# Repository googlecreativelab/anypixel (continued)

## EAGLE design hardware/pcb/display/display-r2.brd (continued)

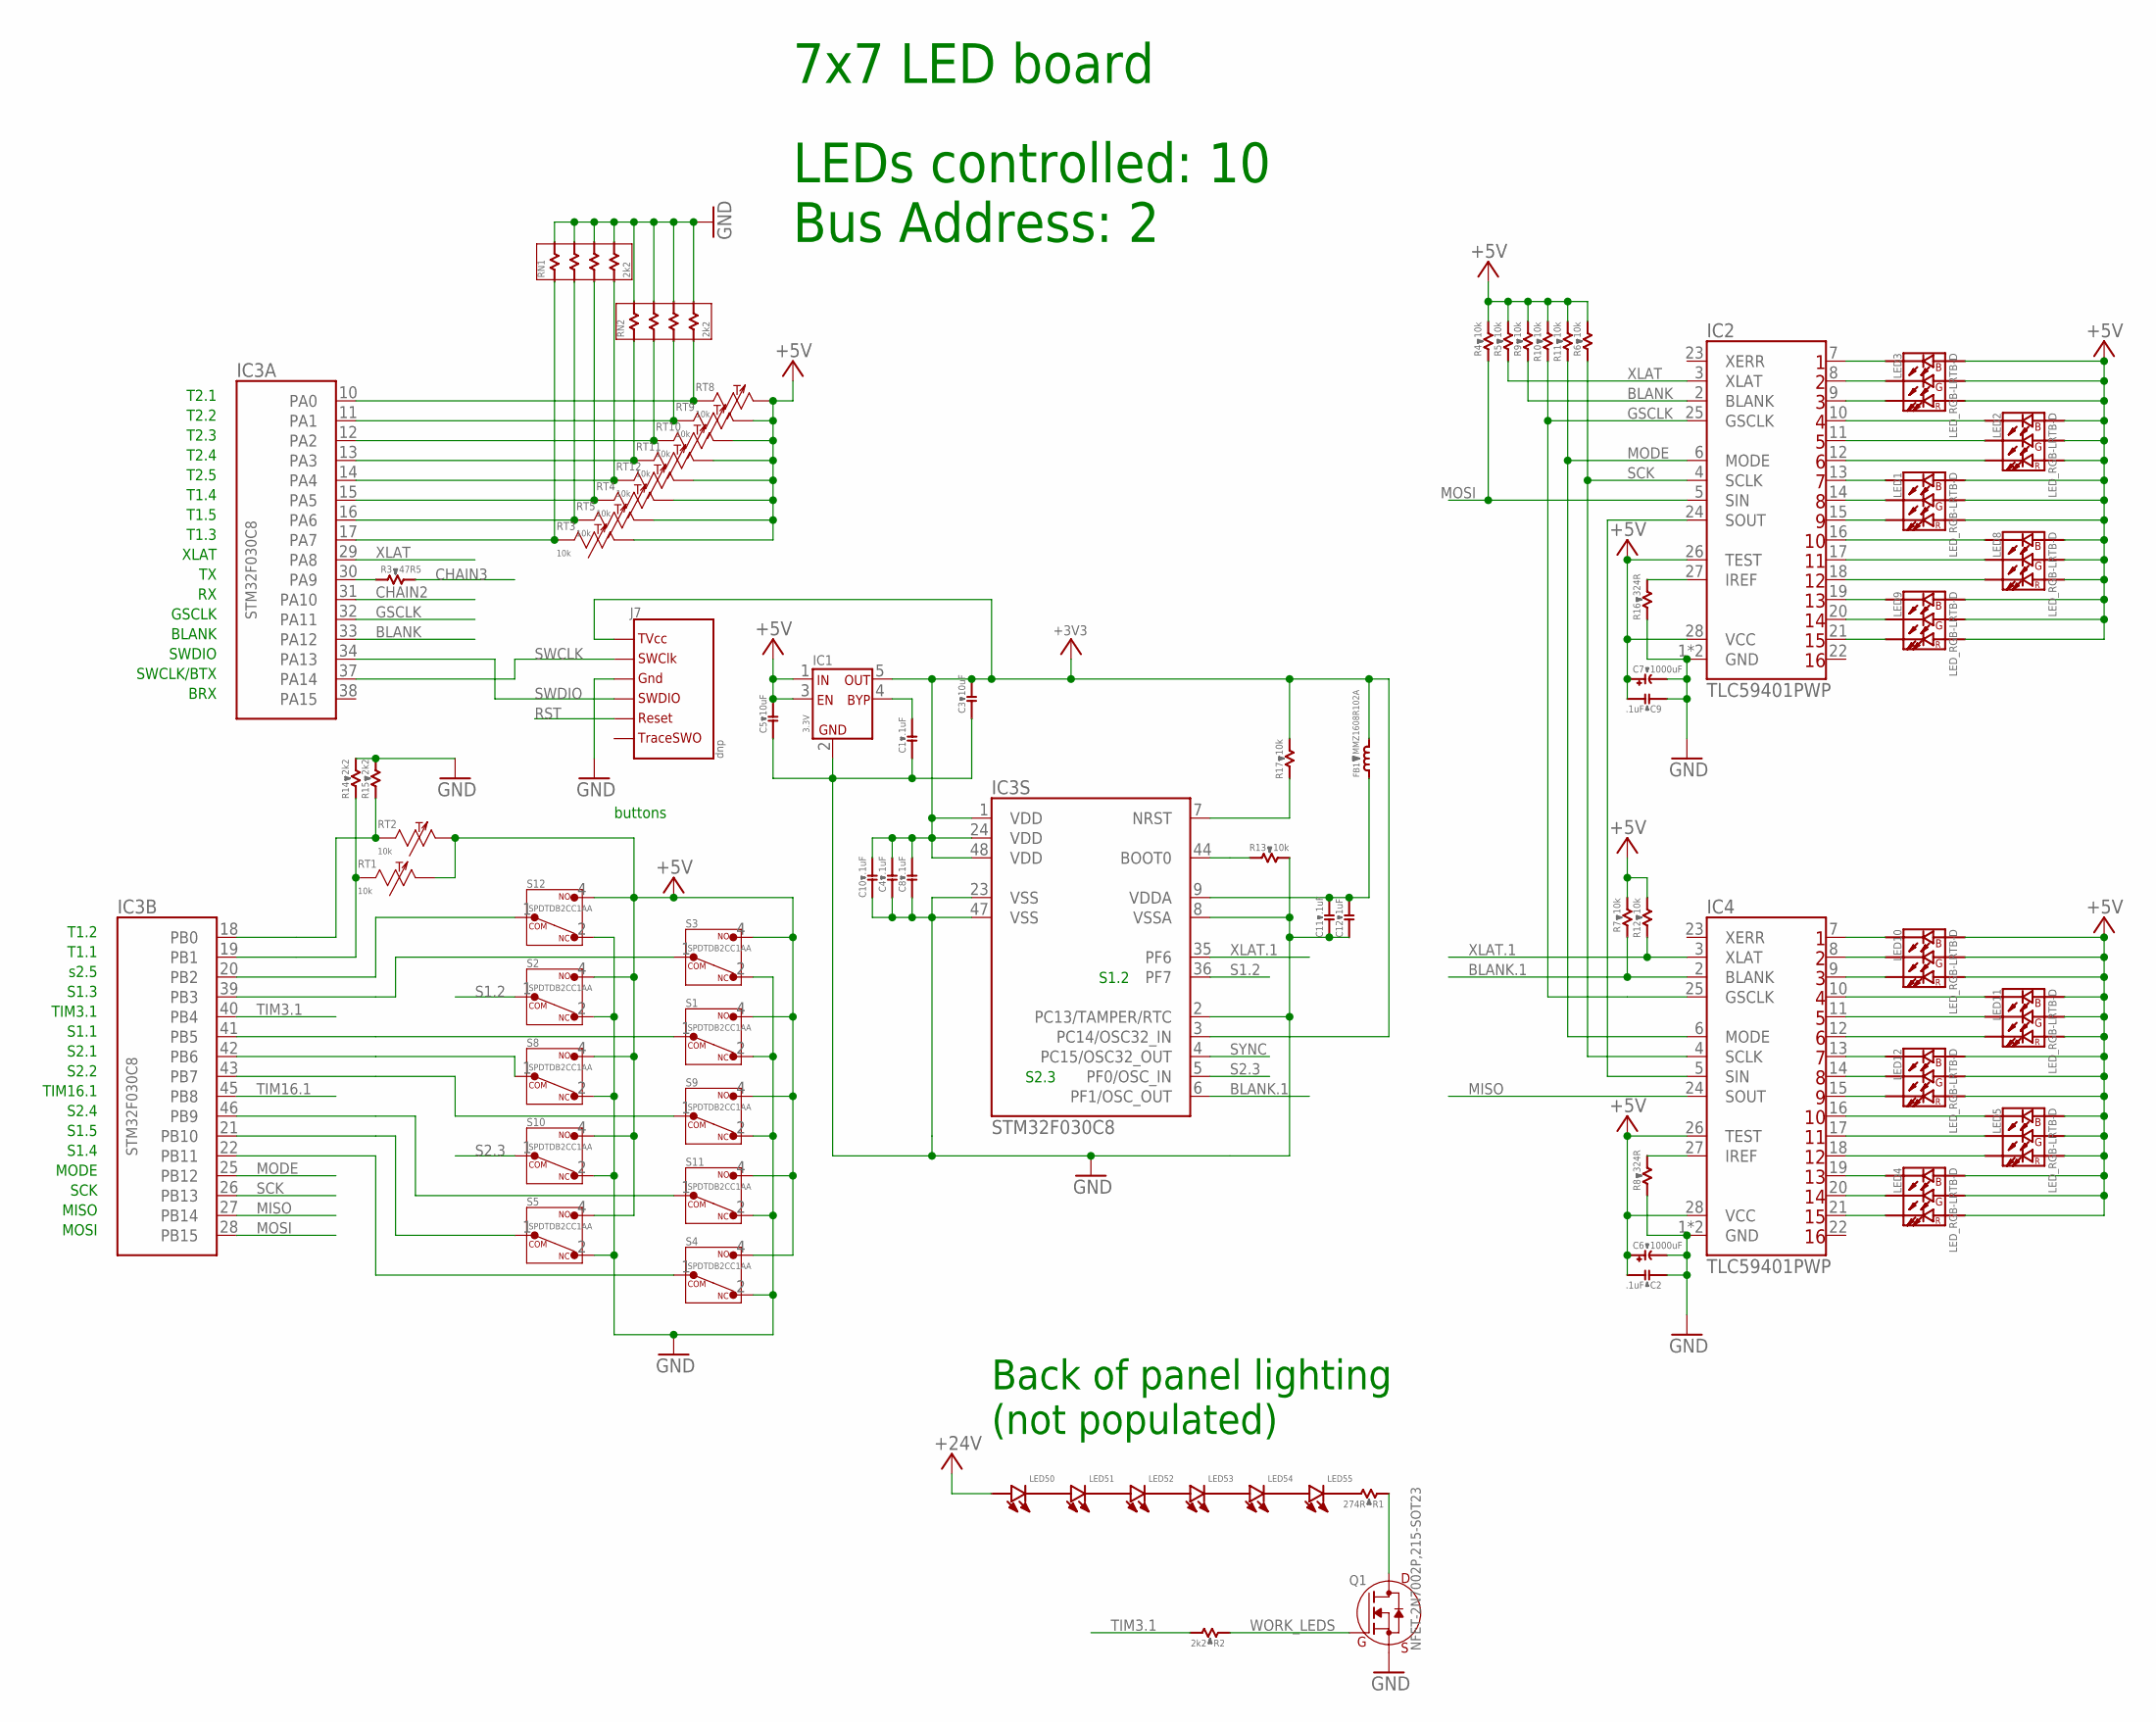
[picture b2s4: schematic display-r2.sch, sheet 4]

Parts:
C1, C2, C4, C8, C9, C10, C11: .1uF; C0603B; PARTNO CGA3E2X7R1H104K080AA
C3, C5: 10uF; C0603B; PARTNO C1608X6S1A106M080AC
C6, C7: 1000uF; E5-10,5; PARTNO EKZN160ELL102MJ16S
C12: 1uF; C0603B; PARTNO CGA3E3X5R1H105K080AB
FB1: MMZ1608R102A; R0603B; PARTNO MMZ1608R102A
IC1: 3.3V; SOT-23-5; PARTNO TC2185-3.3VCTTR
IC2, IC4: TLC59401PWP; TSSOP28_PAD; PARTNO TLC59401PWPR
IC3: STM32F030C8; LQFP-48; PARTNO STM32F030C8T6
J7: dnp; TC2030-IDC-NL
LED1, LED2, LED3, LED4, LED5, LED8, LED9, LED10, LED11, LED12: LED_RGB-LRTB-D; LRTB_C9TP-D; PARTNO LRTBC9TP-CWD5-1+D5E7-25+A
LED50, LED51, LED52, LED53, LED54, LED55: LED-LTW-006DCG; LTW-006DCG; PARTNO LTW-006DCG-E2
Q1: NFET-2N7002P,215-SOT23; SOT-23; PARTNO 2N7002P,215
R1: 274R; R0805B; PARTNO CRCW0805274RFKEA
R2, R14, R15: 2k2; R0603B; PARTNO CRCW06032K20FKEA
R3: 47R5; R0603B; PARTNO CRCW060347R5FKEA
R4, R5, R6, R7, R9, R10, R11, R12, R13, R17: 10k; R0603B; PARTNO CRCW060310K0FKEA
R8, R16: 324R; R0603B; PARTNO CRCW0603324RFKEA
RN1, RN2: 2k2; CAY16; PARTNO CAY16-2201F4LF
RT1, RT2, RT3, RT4, RT5, RT8, RT9, RT10, RT11, RT12: 10k; R0603Y; PARTNO NCP18XH103F03RB
S1, S2, S3, S4, S5, S8, S9, S10, S11, S12: SPDTDB2CC1AA; DB2CC1AA; PARTNO DB2CC1AA

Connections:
+3V3: C3.2, C4.2, C8.2, C10.2, FB1.2, IC1.5 (OUT), IC3.1 (VDD), IC3.3 (PC14/OSC32_IN), IC3.24 (VDD), IC3.48 (VDD), J7.1 (TVCC), R17.2
+5V: C2.2, C5.2, C6.+, C7.+, C9.2, IC1.1 (IN), IC1.3 (EN), IC2.26 (TEST), IC2.28 (VCC), IC4.26 (TEST), IC4.28 (VCC), LED1.A1 (ANODE_R), LED1.A2 (ANODE_G), LED1.A3 (ANODE_B), LED2.A1 (ANODE_R), LED2.A2 (ANODE_G), LED2.A3 (ANODE_B), LED3.A1 (ANODE_R), LED3.A2 (ANODE_G), LED3.A3 (ANODE_B), LED4.A1 (ANODE_R), LED4.A2 (ANODE_G), LED4.A3 (ANODE_B), LED5.A1 (ANODE_R), LED5.A2 (ANODE_G), LED5.A3 (ANODE_B), LED8.A1 (ANODE_R), LED8.A2 (ANODE_G), LED8.A3 (ANODE_B), LED9.A1 (ANODE_R), LED9.A2 (ANODE_G), LED9.A3 (ANODE_B), LED10.A1 (ANODE_R), LED10.A2 (ANODE_G), LED10.A3 (ANODE_B), LED11.A1 (ANODE_R), LED11.A2 (ANODE_G), LED11.A3 (ANODE_B), LED12.A1 (ANODE_R), LED12.A2 (ANODE_G), LED12.A3 (ANODE_B), R4.2, R5.2, R6.2, R7.2, R9.2, R10.2, R11.2, R12.2, RT1.2, RT2.2, RT3.2, RT4.2, RT5.2, RT8.2, RT9.2, RT10.2, RT11.2, RT12.2, S1.4 (NO), S2.4 (NO), S3.4 (NO), S4.4 (NO), S5.4 (NO), S8.4 (NO), S9.4 (NO), S10.4 (NO), S11.4 (NO), S12.4 (NO); also elsewhere on the board
+24V: LED50.A (ANODE); also elsewhere on the board
BLANK: IC2.2 (BLANK), IC3.33 (PA12), R9.1
BLANK.1: IC3.6 (PF1/OSC_OUT), IC4.2 (BLANK), R7.1
CHAIN2: IC3.31 (PA10); also elsewhere on the board
CHAIN3: R3.2; also elsewhere on the board
GND: C1.1, C2.1, C3.1, C4.1, C5.1, C6.-, C7.-, C8.1, C9.1, C10.1, C11.1, C12.1, IC1.2 (GND), IC2.1 (GND), IC2.PAD (GND), IC3.2 (PC13/TAMPER/RTC), IC3.8 (VSSA), IC3.23 (VSS), IC3.47 (VSS), IC4.1 (GND), IC4.PAD (GND), J7.5 (GND), Q1.2 (S), R8.1, R13.2, R14.2, R15.2, R16.1, RN1.A2, RN1.B2, RN1.C2, RN1.D2, RN2.A2, RN2.B2, RN2.C2, RN2.D2, S1.2 (NC), S2.2 (NC), S3.2 (NC), S4.2 (NC), S5.2 (NC), S8.2 (NC), S9.2 (NC), S10.2 (NC), S11.2 (NC), S12.2 (NC); also elsewhere on the board
GSCLK: IC2.25 (GSCLK), IC3.32 (PA11), IC4.25 (GSCLK), R10.1
MISO: IC3.27 (PB14), IC4.24 (SOUT)
MODE: IC2.6 (MODE), IC3.25 (PB12), IC4.6 (MODE), R11.1
MOSI: IC2.5 (SIN), IC3.28 (PB15), R4.1
unnamed: IC3.44 (BOOT0), R13.1
unnamed: IC2.7 (OUT1), LED3.C3 (CATHODE_B)
unnamed: C1.2, IC1.4 (BYPASS)
unnamed: C11.2, C12.2, FB1.1, IC3.9 (VDDA)
unnamed: IC2.8 (OUT2), LED3.C2 (CATHODE_G)
unnamed: IC2.24 (SOUT), IC4.5 (SIN)
unnamed: IC2.9 (OUT3), LED3.C1 (CATHODE_R)
unnamed: IC2.10 (OUT4), LED2.C3 (CATHODE_B)
unnamed: IC2.11 (OUT5), LED2.C2 (CATHODE_G)
unnamed: IC2.12 (OUT6), LED2.C1 (CATHODE_R)
unnamed: IC2.13 (OUT7), LED1.C3 (CATHODE_B)
unnamed: IC4.27 (IREF), R8.2
unnamed: IC2.14 (OUT8), LED1.C2 (CATHODE_G)
unnamed: IC2.15 (OUT9), LED1.C1 (CATHODE_R)
unnamed: IC2.27 (IREF), R16.2
unnamed: IC2.16 (OUT10), LED8.C3 (CATHODE_B)
unnamed: IC2.17 (OUT11), LED8.C2 (CATHODE_G)
unnamed: IC2.18 (OUT12), LED8.C1 (CATHODE_R)
unnamed: IC2.19 (OUT13), LED9.C3 (CATHODE_B)
unnamed: IC2.20 (OUT14), LED9.C2 (CATHODE_G)
unnamed: IC2.21 (OUT15), LED9.C1 (CATHODE_R)
unnamed: IC4.7 (OUT1), LED10.C3 (CATHODE_B)
unnamed: IC4.8 (OUT2), LED10.C2 (CATHODE_G)
unnamed: IC4.9 (OUT3), LED10.C1 (CATHODE_R)
unnamed: IC4.10 (OUT4), LED11.C3 (CATHODE_B)
unnamed: IC4.11 (OUT5), LED11.C2 (CATHODE_G)
unnamed: IC4.12 (OUT6), LED11.C1 (CATHODE_R)
unnamed: IC4.13 (OUT7), LED12.C3 (CATHODE_B)
unnamed: IC4.14 (OUT8), LED12.C2 (CATHODE_G)
unnamed: IC4.15 (OUT9), LED12.C1 (CATHODE_R)
unnamed: IC4.16 (OUT10), LED5.C3 (CATHODE_B)
unnamed: IC4.17 (OUT11), LED5.C2 (CATHODE_G)
unnamed: IC4.18 (OUT12), LED5.C1 (CATHODE_R)
unnamed: IC4.19 (OUT13), LED4.C3 (CATHODE_B)
unnamed: IC4.20 (OUT14), LED4.C2 (CATHODE_G)
unnamed: IC4.21 (OUT15), LED4.C1 (CATHODE_R)
unnamed: IC3.30 (PA9), R3.1
unnamed: Q1.3 (D), R1.1
unnamed: LED55.K (CATHODE), R1.2
unnamed: LED54.K (CATHODE), LED55.A (ANODE)
unnamed: LED53.K (CATHODE), LED54.A (ANODE)
unnamed: LED52.K (CATHODE), LED53.A (ANODE)
unnamed: LED51.K (CATHODE), LED52.A (ANODE)
unnamed: LED50.K (CATHODE), LED51.A (ANODE)
RST: IC3.7 (NRST), J7.3 (RESET), R17.1
S1.1: IC3.41 (PB5), S1.1 (COM)
S1.2: IC3.36 (PF7), S2.1 (COM)
S1.3: IC3.39 (PB3), S3.1 (COM)
S1.4: IC3.22 (PB11), S4.1 (COM)
S1.5: IC3.21 (PB10), S5.1 (COM)
S2.1: IC3.42 (PB6), S8.1 (COM)
S2.2: IC3.43 (PB7), S9.1 (COM)
S2.3: IC3.5 (PF0/OSC_IN), S10.1 (COM)
S2.4: IC3.46 (PB9), S11.1 (COM)
S2.5: IC3.20 (PB2), S12.1 (COM)
SCK: IC2.4 (SCLK), IC3.26 (PB13), IC4.4 (SCLK), R6.1
SWCLK: IC3.37 (PA14), J7.4 (SWCLK)
SWDIO: IC3.34 (PA13), J7.2 (SWDIO)
SYNC: IC3.4 (PC15/OSC32_OUT); also elsewhere on the board
T1: IC3.10 (PA0), RN2.D1, RT8.1
T2: IC3.11 (PA1), RN2.C1, RT9.1
T3: IC3.12 (PA2), RN2.B1, RT10.1
T4: IC3.13 (PA3), RN2.A1, RT11.1
T5: IC3.14 (PA4), RN1.D1, RT12.1
T6: IC3.15 (PA5), RN1.C1, RT4.1
T7: IC3.16 (PA6), RN1.B1, RT5.1
T8: IC3.17 (PA7), RN1.A1, RT3.1
T9: IC3.18 (PB0), R15.1, RT2.1
T10: IC3.19 (PB1), R14.1, RT1.1
TIM3.1: IC3.40 (PB4), R2.2
TIM16.1: IC3.45 (PB8)
WORK_LEDS: Q1.1 (G), R2.1
XLAT: IC2.3 (XLAT), IC3.29 (PA8), R5.1
XLAT.1: IC3.35 (PF6), IC4.3 (XLAT), R12.1

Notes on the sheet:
buttons
s2.5
S1.3
TIM3.1
S1.1
S2.1
S2.2
TIM16.1
S2.4
S1.5
S1.4
T1.1
T1.2
MODE
SCK
MISO
MOSI
T2.1
T2.2
T2.3
T2.4
T2.5
T1.4
T1.5
T1.3
XLAT
GSCLK
BLANK
SWDIO
SWCLK/BTX
BRX
S1.2
S2.3
LEDs controlled: 10 Bus Address: 2
Back of panel lighting (not populated)
7x7 LED board

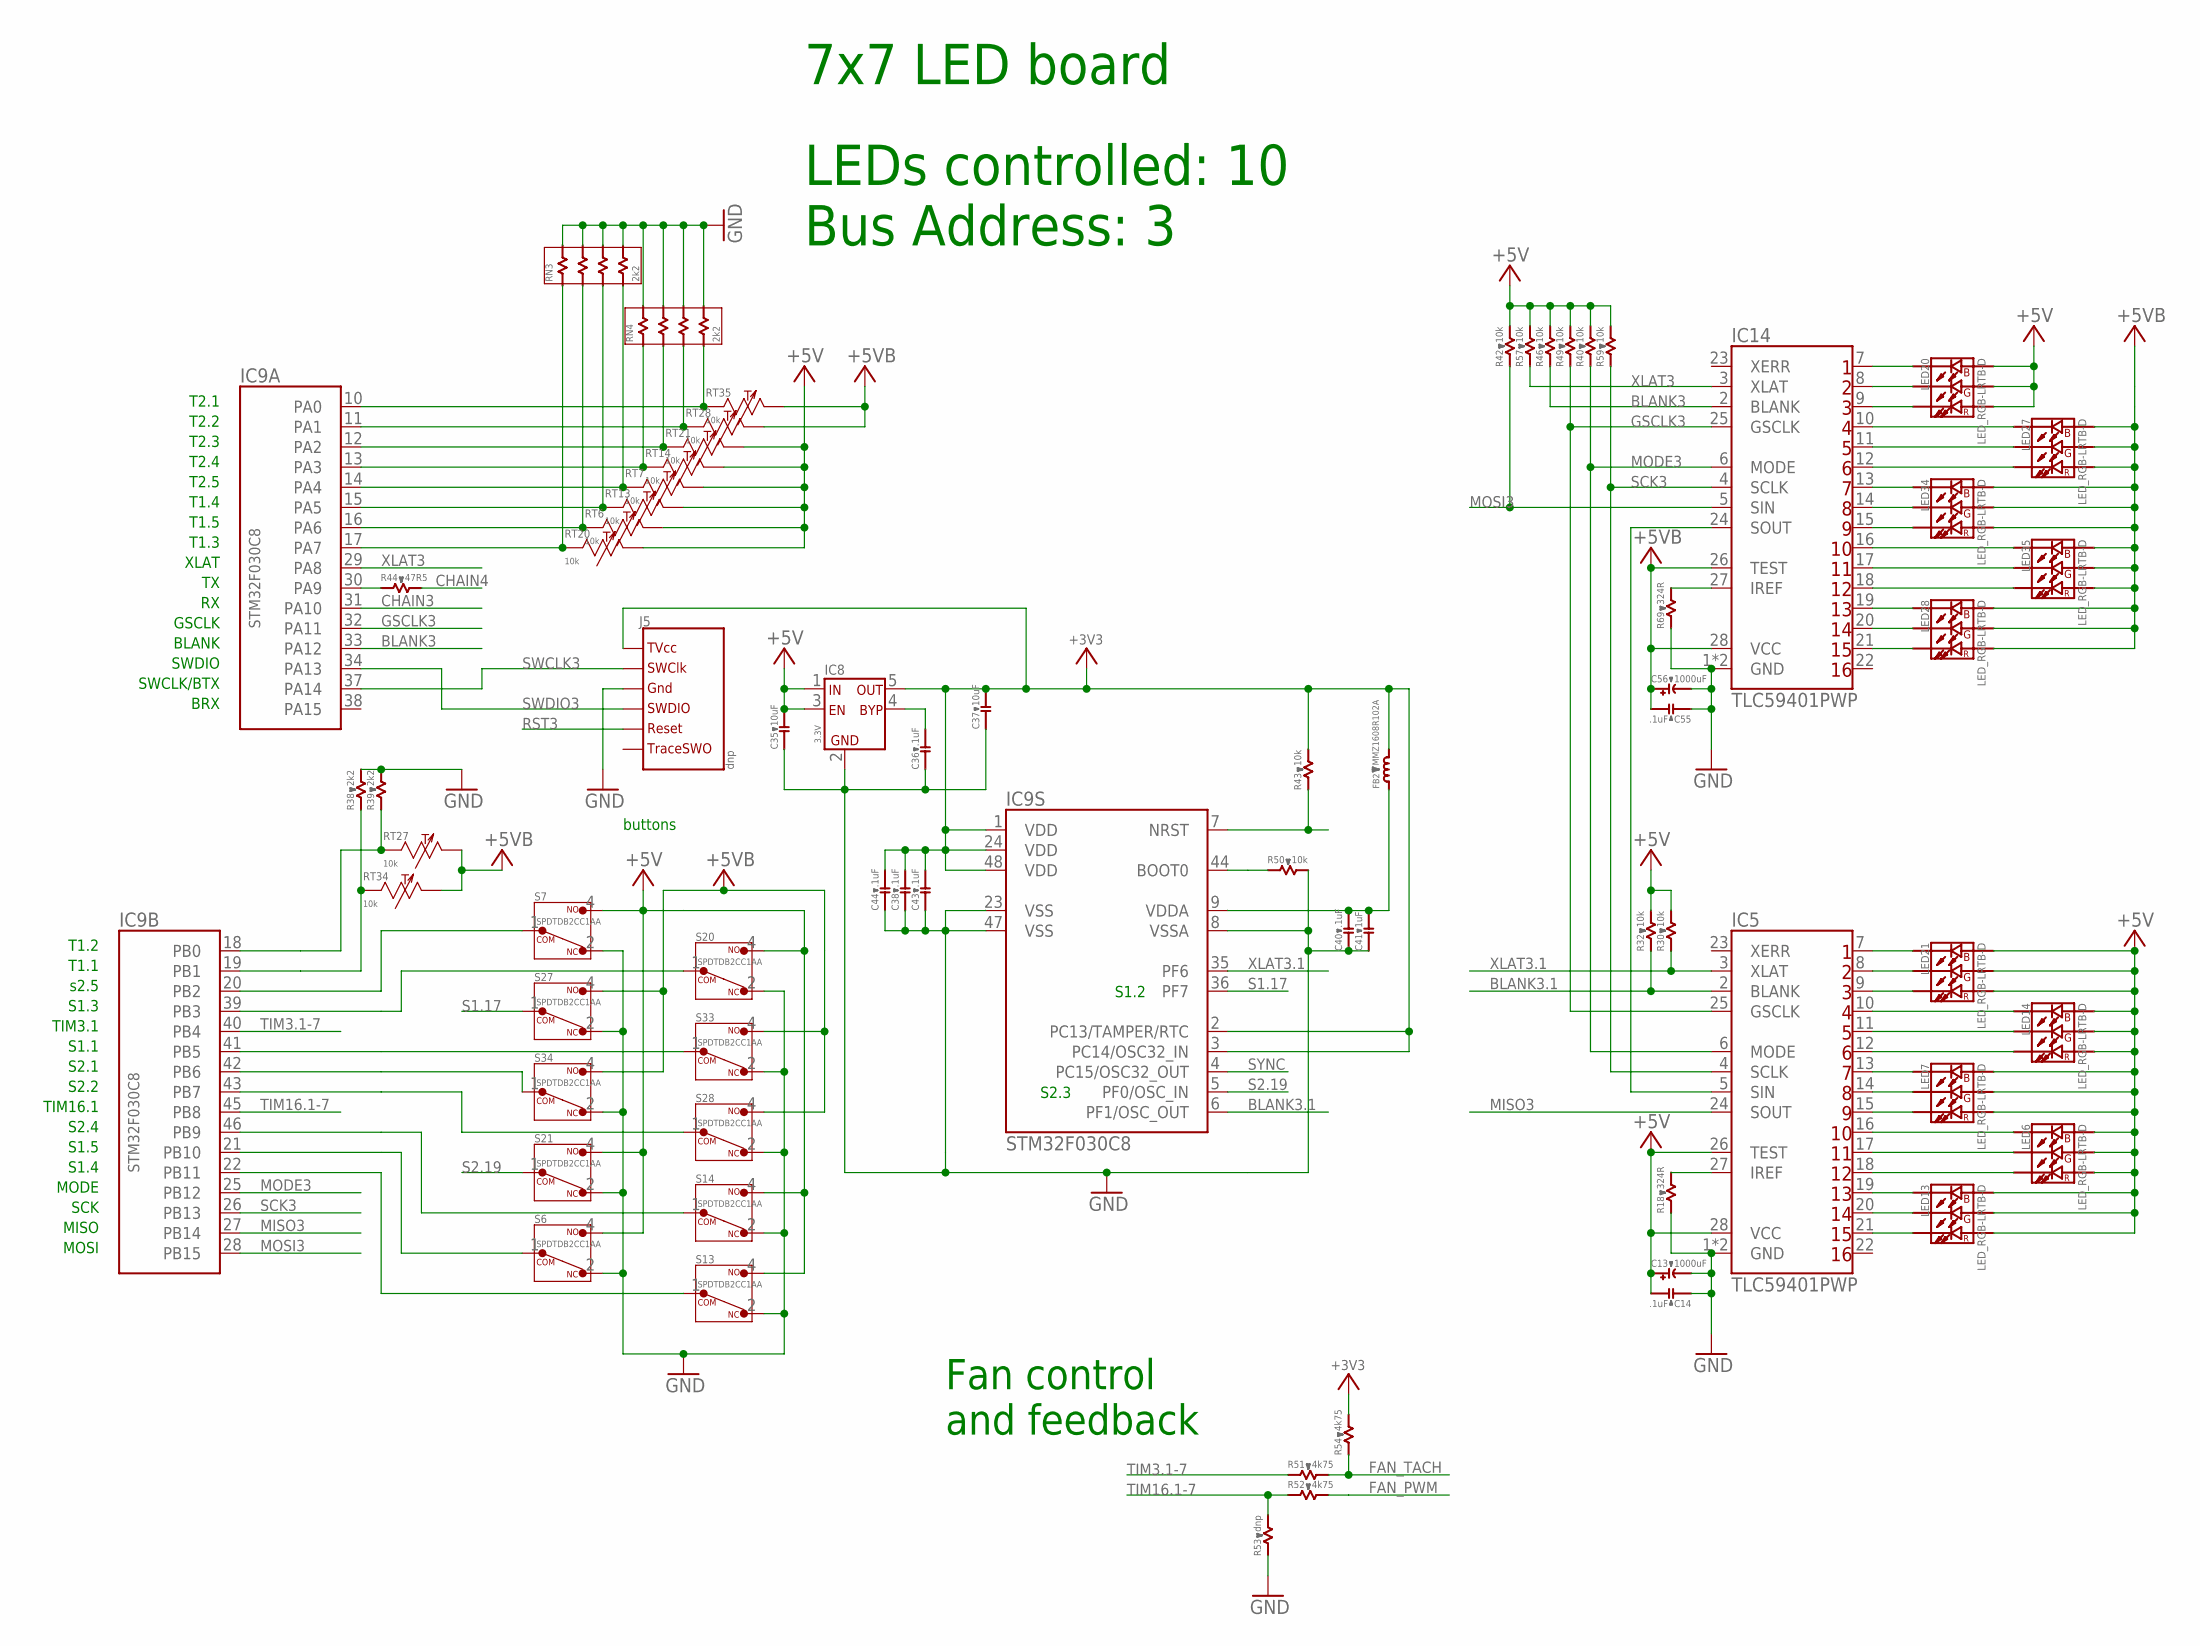
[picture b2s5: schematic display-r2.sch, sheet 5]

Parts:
C13, C56: 1000uF; E5-10,5; PARTNO EKZN160ELL102MJ16S
C14, C36, C38, C40, C43, C44, C55: .1uF; C0603B; PARTNO CGA3E2X7R1H104K080AA
C35, C37: 10uF; C0603B; PARTNO C1608X6S1A106M080AC
C41: 1uF; C0603B; PARTNO CGA3E3X5R1H105K080AB
FB2: MMZ1608R102A; R0603B; PARTNO MMZ1608R102A
IC5, IC14: TLC59401PWP; TSSOP28_PAD; PARTNO TLC59401PWPR
IC8: 3.3V; SOT-23-5; PARTNO TC2185-3.3VCTTR
IC9: STM32F030C8; LQFP-48; PARTNO STM32F030C8T6
J5: dnp; TC2030-IDC-NL
LED6, LED7, LED13, LED14, LED20, LED21, LED27, LED28, LED34, LED35: LED_RGB-LRTB-D; LRTB_C9TP-D; PARTNO LRTBC9TP-CWD5-1+D5E7-25+A
R18, R69: 324R; R0603B; PARTNO CRCW0603324RFKEA
R30, R32, R40, R42, R43, R46, R49, R50, R57, R59: 10k; R0603B; PARTNO CRCW060310K0FKEA
R38, R39: 2k2; R0603B; PARTNO CRCW06032K20FKEA
R44: 47R5; R0603B; PARTNO CRCW060347R5FKEA
R51, R52, R54: 4k75; R0603B; PARTNO CRCW06034K75FKEA
R53: dnp; R0603B; PARTNO *
RN3, RN4: 2k2; CAY16; PARTNO CAY16-2201F4LF
RT6, RT7, RT13, RT14, RT20, RT21, RT27, RT28, RT34, RT35: 10k; R0603Y; PARTNO NCP18XH103F03RB
S6, S7, S13, S14, S20, S21, S27, S28, S33, S34: SPDTDB2CC1AA; DB2CC1AA; PARTNO DB2CC1AA

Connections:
+3V3.D: C37.2, C38.2, C43.2, C44.2, FB2.2, IC8.5 (OUT), IC9.1 (VDD), IC9.2 (PC13/TAMPER/RTC), IC9.3 (PC14/OSC32_IN), IC9.24 (VDD), IC9.48 (VDD), J5.1 (TVCC), R43.2, R54.2
+5V: C13.+, C14.2, C35.2, IC5.26 (TEST), IC5.28 (VCC), IC8.1 (IN), IC8.3 (EN), LED6.A1 (ANODE_R), LED6.A2 (ANODE_G), LED6.A3 (ANODE_B), LED7.A1 (ANODE_R), LED7.A2 (ANODE_G), LED7.A3 (ANODE_B), LED13.A1 (ANODE_R), LED13.A2 (ANODE_G), LED13.A3 (ANODE_B), LED14.A1 (ANODE_R), LED14.A2 (ANODE_G), LED14.A3 (ANODE_B), LED20.A1 (ANODE_R), LED20.A2 (ANODE_G), LED20.A3 (ANODE_B), LED21.A1 (ANODE_R), LED21.A2 (ANODE_G), LED21.A3 (ANODE_B), R30.2, R32.2, R40.2, R42.2, R46.2, R49.2, R57.2, R59.2, RT6.2, RT7.2, RT13.2, RT14.2, RT20.2, RT21.2, S6.4 (NO), S7.4 (NO), S13.4 (NO), S14.4 (NO), S20.4 (NO), S21.4 (NO); also elsewhere on the board
+5VB: C55.2, C56.+, IC14.26 (TEST), IC14.28 (VCC), LED27.A1 (ANODE_R), LED27.A2 (ANODE_G), LED27.A3 (ANODE_B), LED28.A1 (ANODE_R), LED28.A2 (ANODE_G), LED28.A3 (ANODE_B), LED34.A1 (ANODE_R), LED34.A2 (ANODE_G), LED34.A3 (ANODE_B), LED35.A1 (ANODE_R), LED35.A2 (ANODE_G), LED35.A3 (ANODE_B), RT27.2, RT28.2, RT34.2, RT35.2, S27.4 (NO), S28.4 (NO), S33.4 (NO), S34.4 (NO); also elsewhere on the board
BLANK3: IC9.33 (PA12), IC14.2 (BLANK), R46.1
BLANK3.1: IC5.2 (BLANK), IC9.6 (PF1/OSC_OUT), R32.1
CHAIN3: IC9.31 (PA10); also elsewhere on the board
CHAIN4: R44.2; also elsewhere on the board
FAN_PWM: R52.2; also elsewhere on the board
FAN_TACH: R51.2, R54.1; also elsewhere on the board
GND: C13.-, C14.1, C35.1, C36.1, C37.1, C38.1, C40.1, C41.1, C43.1, C44.1, C55.1, C56.-, IC5.1 (GND), IC5.PAD (GND), IC8.2 (GND), IC9.8 (VSSA), IC9.23 (VSS), IC9.47 (VSS), IC14.1 (GND), IC14.PAD (GND), J5.5 (GND), R18.1, R38.2, R39.2, R50.2, R53.1, R69.1, RN3.A2, RN3.B2, RN3.C2, RN3.D2, RN4.A2, RN4.B2, RN4.C2, RN4.D2, S6.2 (NC), S7.2 (NC), S13.2 (NC), S14.2 (NC), S20.2 (NC), S21.2 (NC), S27.2 (NC), S28.2 (NC), S33.2 (NC), S34.2 (NC); also elsewhere on the board
GSCLK3: IC5.25 (GSCLK), IC9.32 (PA11), IC14.25 (GSCLK), R49.1
MISO3: IC5.24 (SOUT), IC9.27 (PB14)
MODE3: IC5.6 (MODE), IC9.25 (PB12), IC14.6 (MODE), R40.1
MOSI3: IC9.28 (PB15), IC14.5 (SIN), R42.1
unnamed: IC9.44 (BOOT0), R50.1
unnamed: C40.2, C41.2, FB2.1, IC9.9 (VDDA)
unnamed: C36.2, IC8.4 (BYPASS)
unnamed: IC5.5 (SIN), IC14.24 (SOUT)
unnamed: IC5.27 (IREF), R18.2
unnamed: IC14.27 (IREF), R69.2
unnamed: IC14.7 (OUT1), LED20.C3 (CATHODE_B)
unnamed: IC14.8 (OUT2), LED20.C2 (CATHODE_G)
unnamed: IC14.9 (OUT3), LED20.C1 (CATHODE_R)
unnamed: IC14.10 (OUT4), LED27.C3 (CATHODE_B)
unnamed: IC14.11 (OUT5), LED27.C2 (CATHODE_G)
unnamed: IC14.12 (OUT6), LED27.C1 (CATHODE_R)
unnamed: IC14.13 (OUT7), LED34.C3 (CATHODE_B)
unnamed: IC14.14 (OUT8), LED34.C2 (CATHODE_G)
unnamed: IC14.15 (OUT9), LED34.C1 (CATHODE_R)
unnamed: IC14.16 (OUT10), LED35.C3 (CATHODE_B)
unnamed: IC14.17 (OUT11), LED35.C2 (CATHODE_G)
unnamed: IC14.18 (OUT12), LED35.C1 (CATHODE_R)
unnamed: IC14.19 (OUT13), LED28.C3 (CATHODE_B)
unnamed: IC14.20 (OUT14), LED28.C2 (CATHODE_G)
unnamed: IC14.21 (OUT15), LED28.C1 (CATHODE_R)
unnamed: IC5.7 (OUT1), LED21.C3 (CATHODE_B)
unnamed: IC5.8 (OUT2), LED21.C2 (CATHODE_G)
unnamed: IC5.9 (OUT3), LED21.C1 (CATHODE_R)
unnamed: IC5.10 (OUT4), LED14.C3 (CATHODE_B)
unnamed: IC5.11 (OUT5), LED14.C2 (CATHODE_G)
unnamed: IC5.12 (OUT6), LED14.C1 (CATHODE_R)
unnamed: IC5.13 (OUT7), LED7.C3 (CATHODE_B)
unnamed: IC5.14 (OUT8), LED7.C2 (CATHODE_G)
unnamed: IC5.15 (OUT9), LED7.C1 (CATHODE_R)
unnamed: IC5.16 (OUT10), LED6.C3 (CATHODE_B)
unnamed: IC5.17 (OUT11), LED6.C2 (CATHODE_G)
unnamed: IC5.18 (OUT12), LED6.C1 (CATHODE_R)
unnamed: IC5.19 (OUT13), LED13.C3 (CATHODE_B)
unnamed: IC5.20 (OUT14), LED13.C2 (CATHODE_G)
unnamed: IC5.21 (OUT15), LED13.C1 (CATHODE_R)
unnamed: IC9.30 (PA9), R44.1
RST3: IC9.7 (NRST), J5.3 (RESET), R43.1
S1.16: IC9.39 (PB3), S20.1 (COM)
S1.17: IC9.36 (PF7), S27.1 (COM)
S1.18: IC9.41 (PB5), S33.1 (COM)
S1.19: IC9.21 (PB10), S6.1 (COM)
S1.20: IC9.22 (PB11), S13.1 (COM)
S2.16: IC9.20 (PB2), S7.1 (COM)
S2.17: IC9.42 (PB6), S34.1 (COM)
S2.18: IC9.43 (PB7), S28.1 (COM)
S2.19: IC9.5 (PF0/OSC_IN), S21.1 (COM)
S2.20: IC9.46 (PB9), S14.1 (COM)
SCK3: IC5.4 (SCLK), IC9.26 (PB13), IC14.4 (SCLK), R59.1
SWCLK3: IC9.37 (PA14), J5.4 (SWCLK)
SWDIO3: IC9.34 (PA13), J5.2 (SWDIO)
SYNC: IC9.4 (PC15/OSC32_OUT); also elsewhere on the board
T31: IC9.14 (PA4), RN3.D1, RT7.1
T32: IC9.15 (PA5), RN3.C1, RT13.1
T33: IC9.16 (PA6), RN3.B1, RT6.1
T34: IC9.17 (PA7), RN3.A1, RT20.1
T35: IC9.18 (PB0), R39.1, RT27.1
T36: IC9.19 (PB1), R38.1, RT34.1
T37: IC9.13 (PA3), RN4.A1, RT14.1
T38: IC9.12 (PA2), RN4.B1, RT21.1
T39: IC9.11 (PA1), RN4.C1, RT28.1
T40: IC9.10 (PA0), RN4.D1, RT35.1
TIM3.1-7: IC9.40 (PB4), R51.1
TIM16.1-7: IC9.45 (PB8), R52.1, R53.2
XLAT3: IC9.29 (PA8), IC14.3 (XLAT), R57.1
XLAT3.1: IC5.3 (XLAT), IC9.35 (PF6), R30.1

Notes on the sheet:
buttons
s2.5
S1.3
TIM3.1
S1.1
S2.1
S2.2
TIM16.1
S2.4
S1.5
S1.4
T1.1
T1.2
MODE
SCK
MISO
MOSI
T2.1
T2.2
T2.3
T2.4
T2.5
T1.4
T1.5
T1.3
XLAT
GSCLK
BLANK
SWDIO
SWCLK/BTX
BRX
S1.2
S2.3
LEDs controlled: 10 Bus Address: 3
Fan control and feedback
7x7 LED board

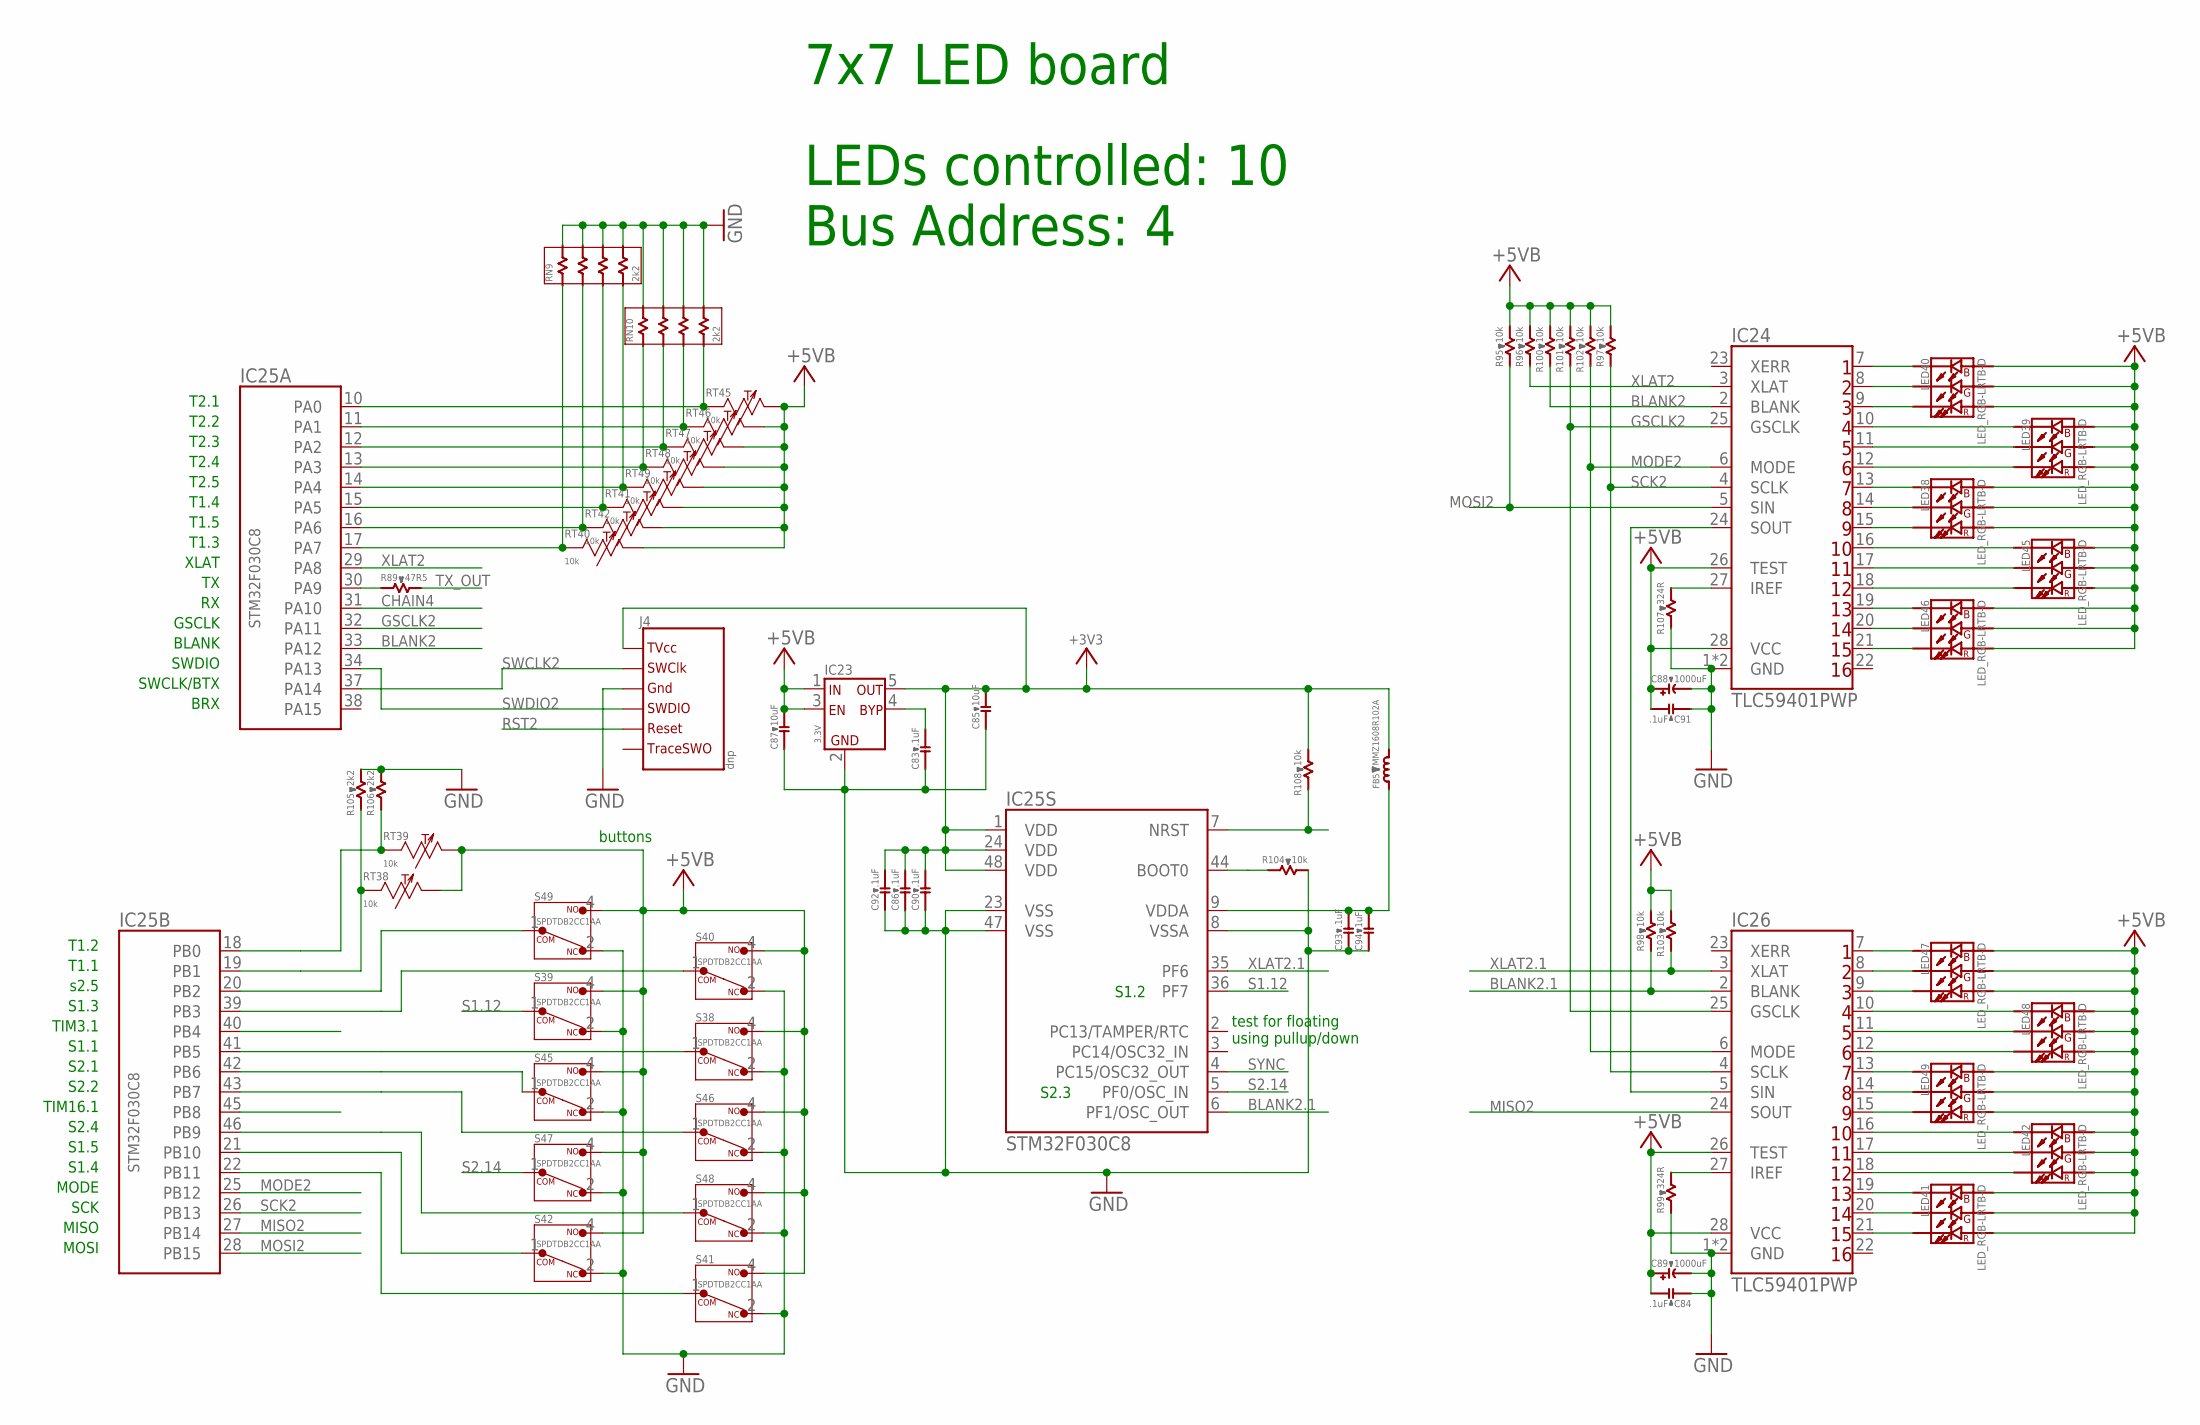
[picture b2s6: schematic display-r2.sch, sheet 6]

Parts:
C83, C84, C86, C90, C91, C92, C93: .1uF; C0603B; PARTNO CGA3E2X7R1H104K080AA
C85, C87: 10uF; C0603B; PARTNO C1608X6S1A106M080AC
C88, C89: 1000uF; E5-10,5; PARTNO EKZN160ELL102MJ16S
C94: 1uF; C0603B; PARTNO CGA3E3X5R1H105K080AB
FB5: MMZ1608R102A; R0603B; PARTNO MMZ1608R102A
IC23: 3.3V; SOT-23-5; PARTNO TC2185-3.3VCTTR
IC24, IC26: TLC59401PWP; TSSOP28_PAD; PARTNO TLC59401PWPR
IC25: STM32F030C8; LQFP-48; PARTNO STM32F030C8T6
J4: dnp; TC2030-IDC-NL
LED38, LED39, LED40, LED41, LED42, LED45, LED46, LED47, LED48, LED49: LED_RGB-LRTB-D; LRTB_C9TP-D; PARTNO LRTBC9TP-CWD5-1+D5E7-25+A
R89: 47R5; R0603B; PARTNO CRCW060347R5FKEA
R95, R96, R97, R98, R100, R101, R102, R103, R104, R108: 10k; R0603B; PARTNO CRCW060310K0FKEA
R99, R107: 324R; R0603B; PARTNO CRCW0603324RFKEA
R105, R106: 2k2; R0603B; PARTNO CRCW06032K20FKEA
RN9, RN10: 2k2; CAY16; PARTNO CAY16-2201F4LF
RT38, RT39, RT40, RT41, RT42, RT45, RT46, RT47, RT48, RT49: 10k; R0603Y; PARTNO NCP18XH103F03RB
S38, S39, S40, S41, S42, S45, S46, S47, S48, S49: SPDTDB2CC1AA; DB2CC1AA; PARTNO DB2CC1AA

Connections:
+3V3.C: C85.2, C86.2, C90.2, C92.2, FB5.2, IC23.5 (OUT), IC25.1 (VDD), IC25.24 (VDD), IC25.48 (VDD), J4.1 (TVCC), R108.2; also elsewhere on the board
+5VB: C84.2, C87.2, C88.+, C89.+, C91.2, IC23.1 (IN), IC23.3 (EN), IC24.26 (TEST), IC24.28 (VCC), IC26.26 (TEST), IC26.28 (VCC), LED38.A1 (ANODE_R), LED38.A2 (ANODE_G), LED38.A3 (ANODE_B), LED39.A1 (ANODE_R), LED39.A2 (ANODE_G), LED39.A3 (ANODE_B), LED40.A1 (ANODE_R), LED40.A2 (ANODE_G), LED40.A3 (ANODE_B), LED41.A1 (ANODE_R), LED41.A2 (ANODE_G), LED41.A3 (ANODE_B), LED42.A1 (ANODE_R), LED42.A2 (ANODE_G), LED42.A3 (ANODE_B), LED45.A1 (ANODE_R), LED45.A2 (ANODE_G), LED45.A3 (ANODE_B), LED46.A1 (ANODE_R), LED46.A2 (ANODE_G), LED46.A3 (ANODE_B), LED47.A1 (ANODE_R), LED47.A2 (ANODE_G), LED47.A3 (ANODE_B), LED48.A1 (ANODE_R), LED48.A2 (ANODE_G), LED48.A3 (ANODE_B), LED49.A1 (ANODE_R), LED49.A2 (ANODE_G), LED49.A3 (ANODE_B), R95.2, R96.2, R97.2, R98.2, R100.2, R101.2, R102.2, R103.2, RT38.2, RT39.2, RT40.2, RT41.2, RT42.2, RT45.2, RT46.2, RT47.2, RT48.2, RT49.2, S38.4 (NO), S39.4 (NO), S40.4 (NO), S41.4 (NO), S42.4 (NO), S45.4 (NO), S46.4 (NO), S47.4 (NO), S48.4 (NO), S49.4 (NO); also elsewhere on the board
BLANK2: IC24.2 (BLANK), IC25.33 (PA12), R100.1
BLANK2.1: IC25.6 (PF1/OSC_OUT), IC26.2 (BLANK), R98.1
CHAIN4: IC25.31 (PA10); also elsewhere on the board
GND: C83.1, C84.1, C85.1, C86.1, C87.1, C88.-, C89.-, C90.1, C91.1, C92.1, C93.1, C94.1, IC23.2 (GND), IC24.1 (GND), IC24.PAD (GND), IC25.8 (VSSA), IC25.23 (VSS), IC25.47 (VSS), IC26.1 (GND), IC26.PAD (GND), J4.5 (GND), R99.1, R104.2, R105.2, R106.2, R107.1, RN9.A2, RN9.B2, RN9.C2, RN9.D2, RN10.A2, RN10.B2, RN10.C2, RN10.D2, S38.2 (NC), S39.2 (NC), S40.2 (NC), S41.2 (NC), S42.2 (NC), S45.2 (NC), S46.2 (NC), S47.2 (NC), S48.2 (NC), S49.2 (NC); also elsewhere on the board
GSCLK2: IC24.25 (GSCLK), IC25.32 (PA11), IC26.25 (GSCLK), R101.1
MISO2: IC25.27 (PB14), IC26.24 (SOUT)
MODE2: IC24.6 (MODE), IC25.25 (PB12), IC26.6 (MODE), R102.1
MOSI2: IC24.5 (SIN), IC25.28 (PB15), R95.1
unnamed: IC25.44 (BOOT0), R104.1
unnamed: C93.2, C94.2, FB5.1, IC25.9 (VDDA)
unnamed: C83.2, IC23.4 (BYPASS)
unnamed: IC24.24 (SOUT), IC26.5 (SIN)
unnamed: IC26.27 (IREF), R99.2
unnamed: IC24.27 (IREF), R107.2
unnamed: IC24.7 (OUT1), LED40.C3 (CATHODE_B)
unnamed: IC24.8 (OUT2), LED40.C2 (CATHODE_G)
unnamed: IC24.9 (OUT3), LED40.C1 (CATHODE_R)
unnamed: IC24.10 (OUT4), LED39.C3 (CATHODE_B)
unnamed: IC24.11 (OUT5), LED39.C2 (CATHODE_G)
unnamed: IC24.12 (OUT6), LED39.C1 (CATHODE_R)
unnamed: IC24.13 (OUT7), LED38.C3 (CATHODE_B)
unnamed: IC24.14 (OUT8), LED38.C2 (CATHODE_G)
unnamed: IC24.15 (OUT9), LED38.C1 (CATHODE_R)
unnamed: IC24.16 (OUT10), LED45.C3 (CATHODE_B)
unnamed: IC24.17 (OUT11), LED45.C2 (CATHODE_G)
unnamed: IC24.18 (OUT12), LED45.C1 (CATHODE_R)
unnamed: IC24.19 (OUT13), LED46.C3 (CATHODE_B)
unnamed: IC24.20 (OUT14), LED46.C2 (CATHODE_G)
unnamed: IC24.21 (OUT15), LED46.C1 (CATHODE_R)
unnamed: IC26.7 (OUT1), LED47.C3 (CATHODE_B)
unnamed: IC26.8 (OUT2), LED47.C2 (CATHODE_G)
unnamed: IC26.9 (OUT3), LED47.C1 (CATHODE_R)
unnamed: IC26.10 (OUT4), LED48.C3 (CATHODE_B)
unnamed: IC26.11 (OUT5), LED48.C2 (CATHODE_G)
unnamed: IC26.12 (OUT6), LED48.C1 (CATHODE_R)
unnamed: IC26.13 (OUT7), LED49.C3 (CATHODE_B)
unnamed: IC26.14 (OUT8), LED49.C2 (CATHODE_G)
unnamed: IC26.15 (OUT9), LED49.C1 (CATHODE_R)
unnamed: IC26.16 (OUT10), LED42.C3 (CATHODE_B)
unnamed: IC26.17 (OUT11), LED42.C2 (CATHODE_G)
unnamed: IC26.18 (OUT12), LED42.C1 (CATHODE_R)
unnamed: IC26.19 (OUT13), LED41.C3 (CATHODE_B)
unnamed: IC26.20 (OUT14), LED41.C2 (CATHODE_G)
unnamed: IC26.21 (OUT15), LED41.C1 (CATHODE_R)
unnamed: IC25.30 (PA9), R89.1
RST2: IC25.7 (NRST), J4.3 (RESET), R108.1
S1.11: IC25.39 (PB3), S40.1 (COM)
S1.12: IC25.36 (PF7), S39.1 (COM)
S1.13: IC25.41 (PB5), S38.1 (COM)
S1.14: IC25.21 (PB10), S42.1 (COM)
S1.15: IC25.22 (PB11), S41.1 (COM)
S2.11: IC25.20 (PB2), S49.1 (COM)
S2.12: IC25.42 (PB6), S45.1 (COM)
S2.13: IC25.43 (PB7), S46.1 (COM)
S2.14: IC25.5 (PF0/OSC_IN), S47.1 (COM)
S2.15: IC25.46 (PB9), S48.1 (COM)
SCK2: IC24.4 (SCLK), IC25.26 (PB13), IC26.4 (SCLK), R97.1
SWCLK2: IC25.37 (PA14), J4.4 (SWCLK)
SWDIO2: IC25.34 (PA13), J4.2 (SWDIO)
SYNC: IC25.4 (PC15/OSC32_OUT); also elsewhere on the board
T21: IC25.14 (PA4), RN9.D1, RT49.1
T22: IC25.15 (PA5), RN9.C1, RT41.1
T23: IC25.16 (PA6), RN9.B1, RT42.1
T24: IC25.17 (PA7), RN9.A1, RT40.1
T25: IC25.18 (PB0), R106.1, RT39.1
T26: IC25.19 (PB1), R105.1, RT38.1
T27: IC25.13 (PA3), RN10.A1, RT48.1
T28: IC25.12 (PA2), RN10.B1, RT47.1
T29: IC25.11 (PA1), RN10.C1, RT46.1
T30: IC25.10 (PA0), RN10.D1, RT45.1
TIM3.3: IC25.40 (PB4)
TIM16.3: IC25.45 (PB8)
TX_OUT: R89.2; also elsewhere on the board
XLAT2: IC24.3 (XLAT), IC25.29 (PA8), R96.1
XLAT2.1: IC25.35 (PF6), IC26.3 (XLAT), R103.1

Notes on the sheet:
buttons
s2.5
S1.3
TIM3.1
S1.1
S2.1
S2.2
TIM16.1
S2.4
S1.5
S1.4
T1.1
T1.2
MODE
SCK
MISO
MOSI
T2.1
T2.2
T2.3
T2.4
T2.5
T1.4
T1.5
T1.3
XLAT
GSCLK
BLANK
SWDIO
SWCLK/BTX
BRX
S1.2
S2.3
test for floating using pullup/down
LEDs controlled: 10 Bus Address: 4
7x7 LED board
